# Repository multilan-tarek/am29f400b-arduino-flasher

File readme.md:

## Am29F400B Arduino Flasher

This is a script for reading, erasing and writing the AMD Am29F400B flash memory chips using an Arduino MEGA.  
These chips were used in many ECUs, TCUs and other kinds of control units in combination with the CR167 CPU from Siemens/Infineon.

### Supported Chips

```
Am29F400BT                  | Top Boot Sector
Am29F400BB                  | Bottom Boot Sector
```

***

## Software

The PC side script needs to be executed using Python 3 in a shell. (https://www.python.org/downloads/)

Flash the `arduino.ino` to an Arduino MEGA.

### Available Commands

```
-r <file>                   | Read full
-r <file> <start> <size>    | Read partial
-r <file> <sector>          | Read sector
-w <file>                   | Write full
-w <file> <start> <size>    | Write partial (without erasing)
-w <file> <sector>          | Write sector
-e                          | Erase full
-e <sector>                 | Erase sector
-v                          | Prints sector protection states
```

***

### Reading

Read all 512KB of data:
```
python3 main.py -r dump.bin
```

Read only data in a specific sector (e.g. SA1, see table below):
```
python3 main.py -r dump.bin 1
```

Read only a specific range (e.g. address 0x10, size 0x200, decimal and hex possible):
```
python3 main.py -r dump.bin 1 0x10 0x200
```
```
python3 main.py -r dump.bin 1 16 512
```
***

### Writing

Write to all 512KB of available space:
```
python3 main.py -w new_data.bin
```

Write only to a specific sector (e.g. SA3, see table below): 
```
python3 main.py -w new_data.bin 3
```

Write only to a specific range (e.g. address 0x20, size 0x100, decimal and hex possible): 
```
python3 main.py -r new_data.bin 1 0x20 0x00
```
```
python3 main.py -r new_data.bin 1 32 256
```

**Attention:**  
Writing to a specific range will not erase the data beforehand, because it is only possible to erase a whole sector.  
So this only works if the bits you want to change are 1.   
You can only change bits back from 0 to 1 with erasing.

Also, any writing can only be done if the sector is unprotected.  
Check the sector protection states using the `-v` command.

***

### Erasing
Erase all sectors (SA0 - SA10)
```
python3 main.py -e
```

Erase only a specific sector (e.g. SA5, see table below)
```
python3 main.py -e 5
```

**Attention:**  
Erasing can only be done if the sector is unprotected.  
Check the sector protection states using the `-v` command.

***

## Hardware

Included is a simple PCB that adapts the 36 pin connector of the Arduino MEGA to the SO44 footprint.  
Use a 1206 1kΩ resistor to pull up the RY/BY# signal. (only needed for erasing and writing)

The gerber file is ready for ordering at JLCPCB.

***

## Sector Layouts
The chip is seperated into 11 sectors.  
Sizes and addresses of these sectors are dependent on the variant.  
Hardware and software is designed to operate in *byte mode*.  
Values would differ in *word mode*.

### Am29F400BT

| Sector | Address | Size    |
|--------|---------|---------|
| SA0    | 0x00000 | 0x10000 |
| SA1    | 0x10000 | 0x10000 |
| SA2    | 0x20000 | 0x10000 |
| SA3    | 0x30000 | 0x10000 |
| SA4    | 0x40000 | 0x10000 |
| SA5    | 0x50000 | 0x10000 |
| SA6    | 0x60000 | 0x10000 |
| SA7    | 0x70000 | 0x8000  |
| SA8    | 0x78000 | 0x2000  |
| SA9    | 0x7a000 | 0x2000  |
| SA10   | 0x7c000 | 0x4000  |

### Am29F400BB

| Sector | Address | Size    |
|--------|---------|---------|
| SA0    | 0x00000 | 0x4000  |
| SA1    | 0x04000 | 0x2000  |
| SA2    | 0x06000 | 0x2000  |
| SA3    | 0x08000 | 0x8000  |
| SA4    | 0x10000 | 0x10000 |
| SA5    | 0x20000 | 0x10000 |
| SA6    | 0x30000 | 0x10000 |
| SA7    | 0x40000 | 0x10000 |
| SA8    | 0x50000 | 0x10000 |
| SA9    | 0x60000 | 0x10000 |
| SA10   | 0x70000 | 0x10000 |

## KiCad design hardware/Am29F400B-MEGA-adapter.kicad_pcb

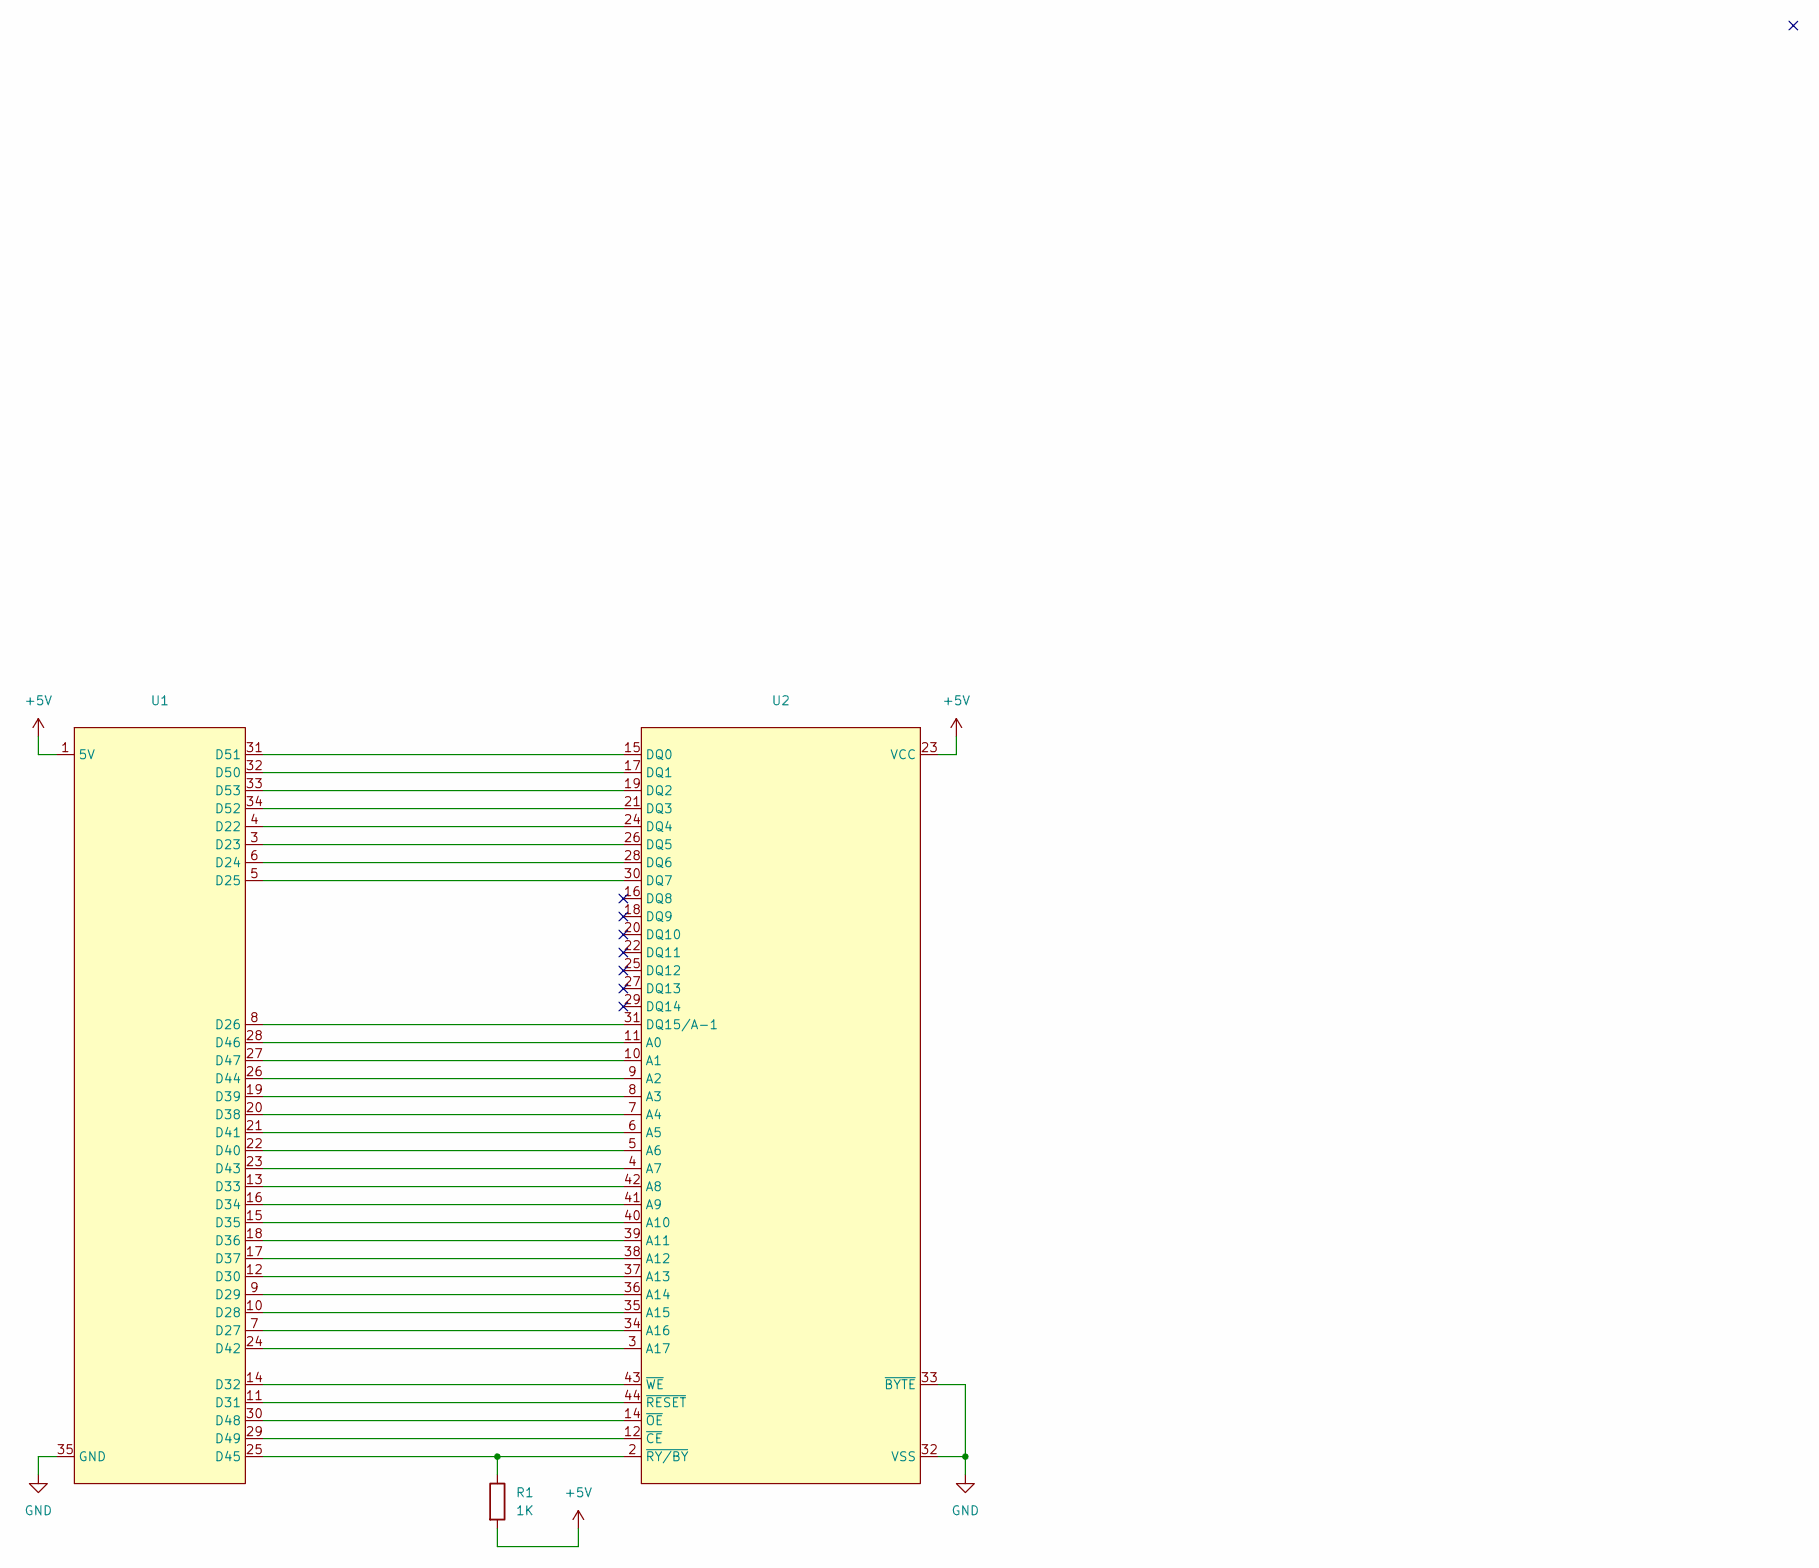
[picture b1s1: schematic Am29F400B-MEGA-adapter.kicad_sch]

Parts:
R1: 1K; R_1206_3216Metric_Pad1.30x1.75mm_HandSolder
U1: PinHeader_2x18_P2.54mm_Vertical
U2: SOP-44_13.3x28.2mm_P1.27mm

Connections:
+5V: R1.2, U1.1 (5V), U1.2 (5V), U2.23 (VCC)
GND: U1.35 (GND), U1.36 (GND), U2.13 (VSS), U2.32 (VSS), U2.33 (~BYTE)
unnamed: U1.4 (D22), U2.24 (DQ4)
unnamed: U1.3 (D23), U2.26 (DQ5)
unnamed: U1.6 (D24), U2.28 (DQ6)
unnamed: U1.5 (D25), U2.30 (DQ7)
unnamed: U1.8 (D26), U2.31 (DQ15/A-1)
unnamed: U1.7 (D27), U2.34 (A16)
unnamed: U1.10 (D28), U2.35 (A15)
unnamed: U1.9 (D29), U2.36 (A14)
unnamed: U1.12 (D30), U2.37 (A13)
unnamed: U1.11 (D31), U2.44 (~RESET)
unnamed: U1.14 (D32), U2.43 (~WE)
unnamed: U1.13 (D33), U2.42 (A8)
unnamed: U1.16 (D34), U2.41 (A9)
unnamed: U1.15 (D35), U2.40 (A10)
unnamed: U1.18 (D36), U2.39 (A11)
unnamed: U1.17 (D37), U2.38 (A12)
unnamed: U1.20 (D38), U2.7 (A4)
unnamed: U1.19 (D39), U2.8 (A3)
unnamed: U1.22 (D40), U2.5 (A6)
unnamed: U1.21 (D41), U2.6 (A5)
unnamed: U1.24 (D42), U2.3 (A17)
unnamed: U1.23 (D43), U2.4 (A7)
unnamed: U1.26 (D44), U2.9 (A2)
unnamed: R1.1, U1.25 (D45), U2.2 (~RY/BY)
unnamed: U1.28 (D46), U2.11 (A0)
unnamed: U1.27 (D47), U2.10 (A1)
unnamed: U1.30 (D48), U2.14 (~OE)
unnamed: U1.29 (D49), U2.12 (~CE)
unnamed: U1.32 (D50), U2.17 (DQ1)
unnamed: U1.31 (D51), U2.15 (DQ0)
unnamed: U1.34 (D52), U2.21 (DQ3)
unnamed: U1.33 (D53), U2.19 (DQ2)

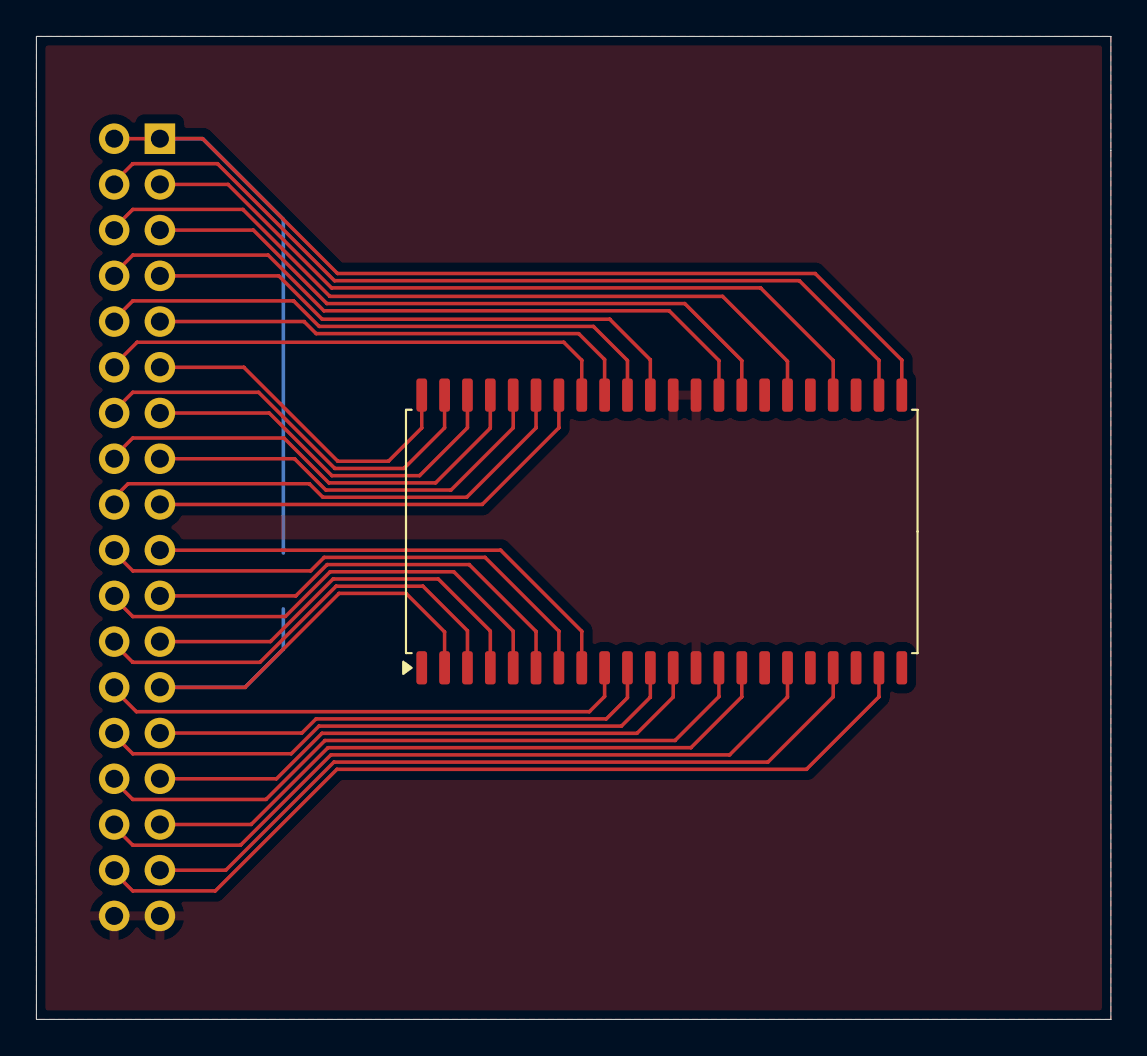
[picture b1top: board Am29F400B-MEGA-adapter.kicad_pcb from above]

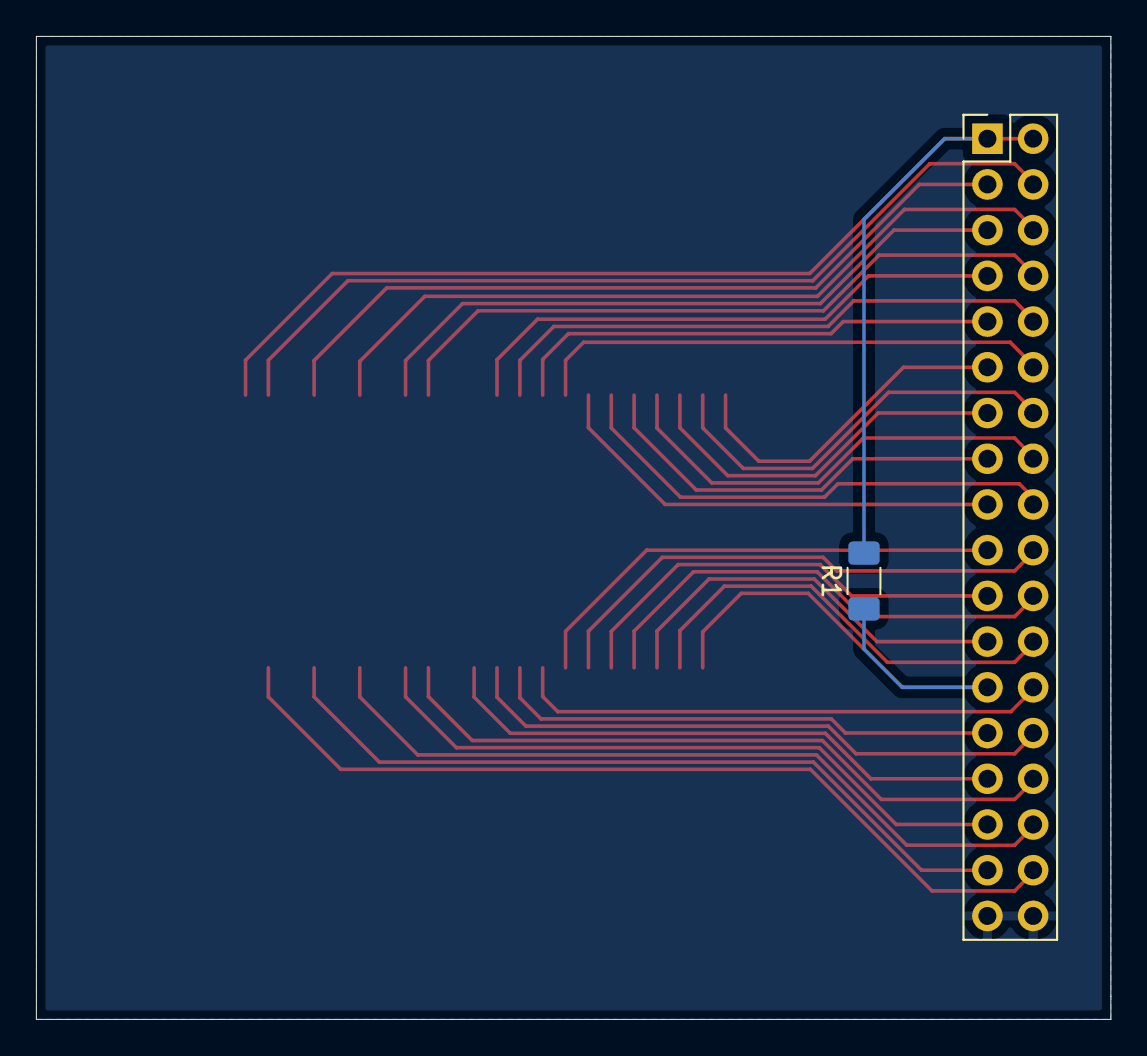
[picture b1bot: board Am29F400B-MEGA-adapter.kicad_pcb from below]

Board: 2 copper layers, 59.7 x 54.6 mm, 3 parts (2 on the bottom side), 34 nets.

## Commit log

2025-03-25 added python script
2025-03-25 arduino.ino modified
2025-03-27 Working version
2025-04-08 Added PCB
2025-04-13 Updated Pin Settings
2025-04-13 Added erase and write to arduino.ino
2025-04-14 Added sector protection check to arduino.ino
2025-04-14 Added erase, write and sector protection check commands to python script
2025-04-14 Fixed typos
2025-04-14 Added device name printout
2025-04-14 Some Hardware Changes
2025-04-14 Removed import
2025-04-20 Fully working software
2025-04-20 Added resistor to rdy/bsy line
2025-04-20 Added readme.md
2025-04-20 added requirements.txt
2025-08-03 Removed unnecessary waits
2026-01-13 Added manufacturer Fujitsu and removed exit() for the case the manufacturer is unknown.
2026-01-30 Corrected Serial Open
2026-04-19 Add license
